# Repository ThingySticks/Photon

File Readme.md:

Photon Prototyping PCB.
=======================

Prototype board for Particle Photon.

See individual versions for PCB specifics.

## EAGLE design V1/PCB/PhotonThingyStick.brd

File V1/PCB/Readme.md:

Photon Prototyping PCB.
=======================

Prototype board for Particle Photon.

Features:
---------

* USB power in via A Connector on left edge or B Connector on Photon. (Do not connect both at once).
* Pull-up or down 1206 pads on A0-A7. Suitable for 1206 or 0805 components.
* LED/Resistor/Capacitor 1206 pads Right edge along with 10 x 2 header for off board connection (8 pins to 1206's + 2v2 & GND).
* 4 1206 pads top/bottom by end of Photon connected to pins to the right of the pad. Ideal of Capacitors, Resistor or LED.
* 3 Mounting holes to allow board to be mounted in case for final use.
* SOT-23 FET/Transistor under Photon with Gate/Base 1206 guard and pull down resistor options.

Mounting:
---------

Single hole middle PCB (at 14.5, 22)
Double holes end PCB (at 76,4 & 76,40)

Size:
-----
Length: 80mm
Width: 44mm

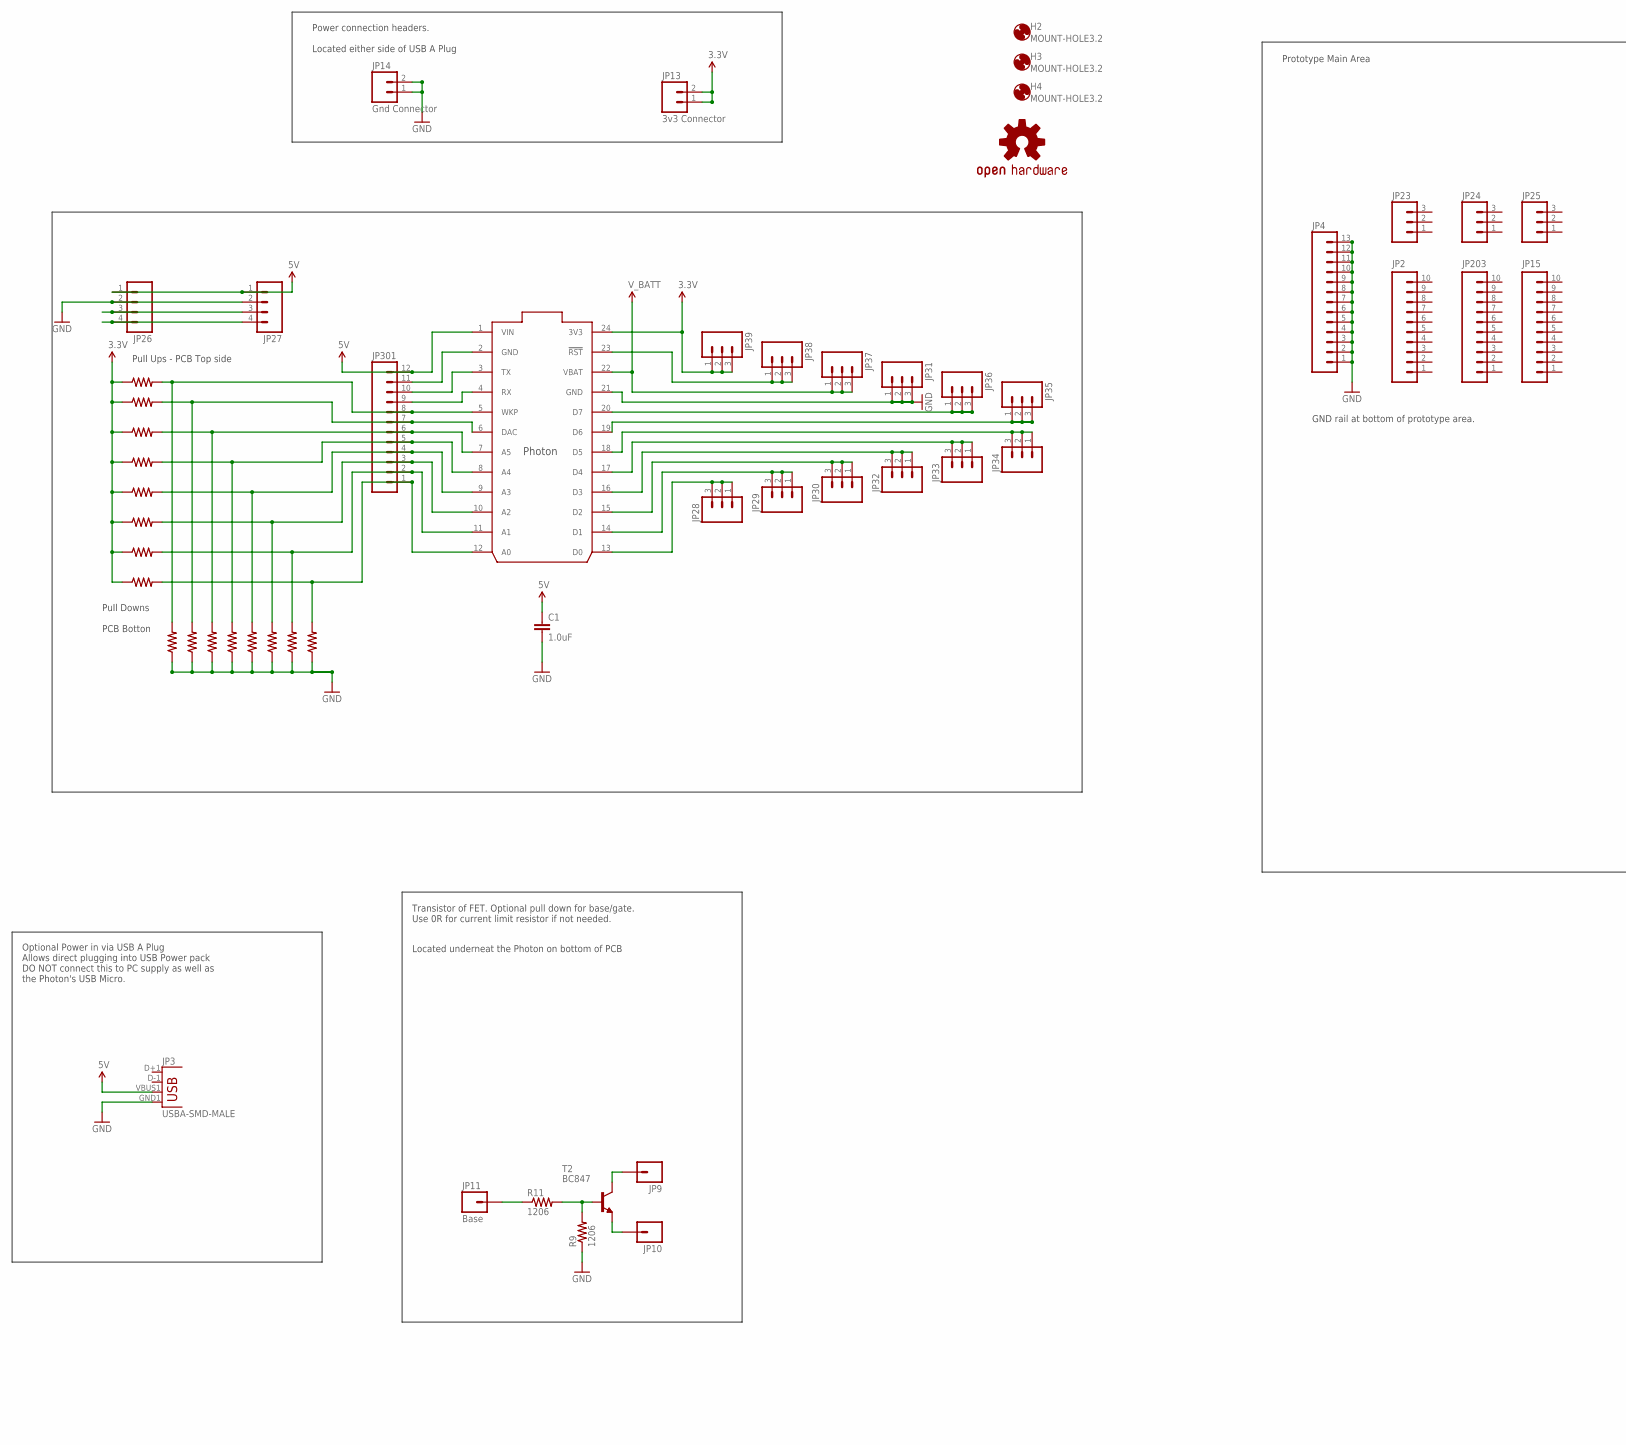
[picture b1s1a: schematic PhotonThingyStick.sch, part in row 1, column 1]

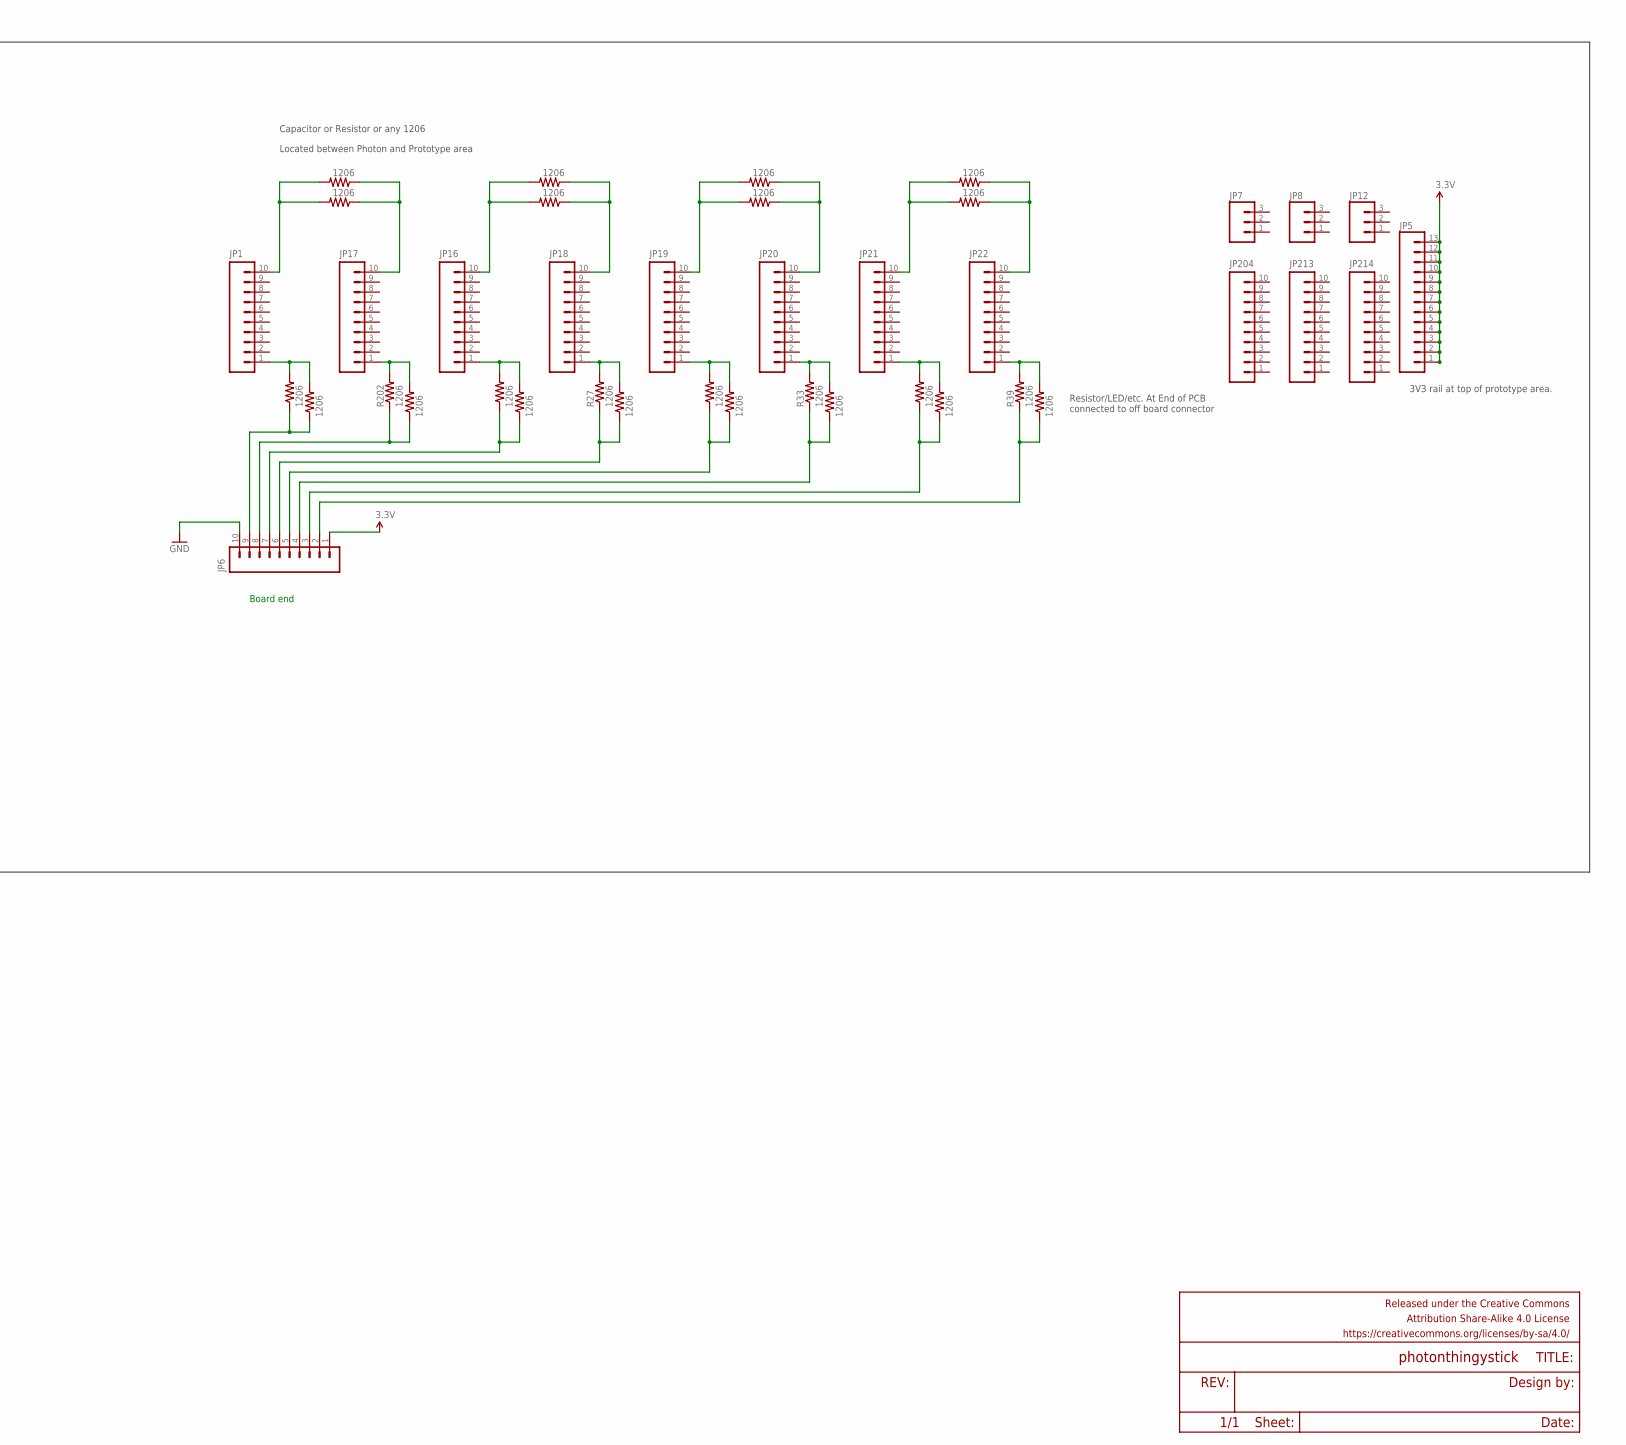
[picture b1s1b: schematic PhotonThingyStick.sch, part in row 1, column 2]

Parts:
C1: 1.0uF; 0805-CAP
FRAME1: FRAME-LEDGER; CREATIVE_COMMONS
H2, H3, H4: MOUNT-HOLE3.2; 3,2
IC1: PHOTON_WITH_HEADERS; PHOTON
JP1, JP2, JP6, JP15, JP16, JP17, JP18, JP19, JP20, JP21, JP22, JP203, JP204, JP213, JP214: M10NO_SILK_PTH_FEMALE; 1X10_NO_SILK
JP3: USBA-SMD-MALE; USB-A-SMT-MALE
JP4, JP5: M13; 1X13
JP7, JP8, JP12, JP23, JP24, JP25: M031X03_NO_SILK; 1X03_NO_SILK
JP9, JP10: M01PTH; 1X01
JP11: Base; 1X01
JP13: 3v3 Connector; 1X02
JP14: Gnd Connector; 1X02
JP26, JP27: M041X04_NO_SILK; 1X04_NO_SILK
JP28, JP29, JP30, JP31, JP32, JP33, JP34, JP35, JP36, JP37, JP38, JP39: M03PTH; 1X03
JP301: M12PTH; 1X12
LOGO1: OSHW-LOGOM; OSHW-LOGO-M
R1, R2, R3, R4, R5, R6, R7, R8, R9, R10, R11, R12, R13, R14, R19, R20, R21, R22, R23, R24, R25, R26, R27, R28, R29, R30, R31, R32, R33, R34, R35, R36, R37, R38, R39, R40, R41, R42, R43, R44, R201, R202: 1206
T2: BC847; SOT23

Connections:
3.3V: IC1.24 (3V3), JP5.1, JP5.2, JP5.3, JP5.4, JP5.5, JP5.6, JP5.7, JP5.8, JP5.9, JP5.10, JP5.11, JP5.12, JP5.13, JP6.1, JP13.1, JP13.2, JP39.1, JP39.2, JP39.3, R1.1, R2.1, R3.1, R4.1, R5.1, R6.1, R7.1, R12.1
5V: C1.1, IC1.1 (VIN), JP3.VBUS1 (VBUS), JP26.1, JP27.1, JP301.12
GND: C1.2, IC1.2 (GND), IC1.21 (GND), JP3.GND1 (GND), JP4.1, JP4.2, JP4.3, JP4.4, JP4.5, JP4.6, JP4.7, JP4.8, JP4.9, JP4.10, JP4.11, JP4.12, JP4.13, JP6.10, JP14.1, JP14.2, JP26.2, JP27.2, JP31.1, JP31.2, JP31.3, JP301.11, R8.1, R9.1, R10.1, R13.1, R14.1, R19.1, R20.1, R21.1, R22.1
unnamed: JP17.1, R26.2, R202.2
unnamed: JP1.1, R23.2, R201.2
unnamed: IC1.5 (WKP), JP301.8, R8.2, R12.2
unnamed: IC1.6 (DAC), JP301.7, R5.2, R10.2
unnamed: IC1.7 (A5), JP301.6, R1.2, R13.2
unnamed: IC1.8 (A4), JP301.5, R2.2, R14.2
unnamed: IC1.9 (A3), JP301.4, R3.2, R19.2
unnamed: IC1.10 (A2), JP301.3, R4.2, R20.2
unnamed: IC1.11 (A1), JP301.2, R6.2, R21.2
unnamed: IC1.12 (A0), JP301.1, R7.2, R22.2
unnamed: JP6.9, R23.1, R201.1
unnamed: IC1.18 (D5), JP34.1, JP34.2, JP34.3
unnamed: IC1.17 (D4), JP33.1, JP33.2, JP33.3
unnamed: IC1.16 (D3), JP32.1, JP32.2, JP32.3
unnamed: IC1.15 (D2), JP30.1, JP30.2, JP30.3
unnamed: IC1.14 (D1), JP29.1, JP29.2, JP29.3
unnamed: IC1.13 (D0), JP28.1, JP28.2, JP28.3
unnamed: JP1.10, R24.2, R25.2
unnamed: IC1.23 (!RST), JP38.1, JP38.2, JP38.3
unnamed: JP17.10, R24.1, R25.1
unnamed: JP6.8, R26.1, R202.1
unnamed: JP18.1, R27.2, R32.2
unnamed: JP16.1, R28.2, R29.2
unnamed: JP6.7, R28.1, R29.1
unnamed: JP16.10, R30.2, R31.2
unnamed: JP18.10, R30.1, R31.1
unnamed: JP6.6, R27.1, R32.1
unnamed: JP20.1, R33.2, R38.2
unnamed: IC1.20 (D7), JP36.1, JP36.2, JP36.3
unnamed: IC1.19 (D6), JP35.1, JP35.2, JP35.3
unnamed: JP19.1, R34.2, R35.2
unnamed: JP6.5, R34.1, R35.1
unnamed: JP19.10, R36.2, R37.2
unnamed: JP20.10, R36.1, R37.1
unnamed: JP6.4, R33.1, R38.1
unnamed: JP22.1, R39.2, R44.2
unnamed: JP11.1, R11.1
unnamed: R9.2, R11.2, T2.1 (B)
unnamed: JP9.1, T2.3 (C)
unnamed: JP10.1, T2.2 (E)
unnamed: JP21.1, R40.2, R41.2
unnamed: JP6.3, R40.1, R41.1
unnamed: JP21.10, R42.2, R43.2
unnamed: JP22.10, R42.1, R43.1
unnamed: JP6.2, R39.1, R44.1
RX: IC1.4 (RX), JP26.4, JP27.4, JP301.9
TX: IC1.3 (TX), JP26.3, JP27.3, JP301.10
V_BATT: IC1.22 (VBAT), JP37.1, JP37.2, JP37.3

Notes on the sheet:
Prototype Main Area
Board end
Pull Ups - PCB Top side
Pull Downs PCB Botton
Capacitor or Resistor or any 1206
Located between Photon and Prototype area
Resistor/LED/etc. At End of PCB connected to off board connector
Transistor of FET. Optional pull down for base/gate. Use 0R for current limit resistor if not needed.
Located underneat the Photon on bottom of PCB
Optional Power in via USB A Plug Allows direct plugging into USB Power pack DO NOT connect this to PC supply as well as the Photon's USB Micro.
Power connection headers. Located either side of USB A Plug
GND rail at bottom of prototype area.
3V3 rail at top of prototype area.

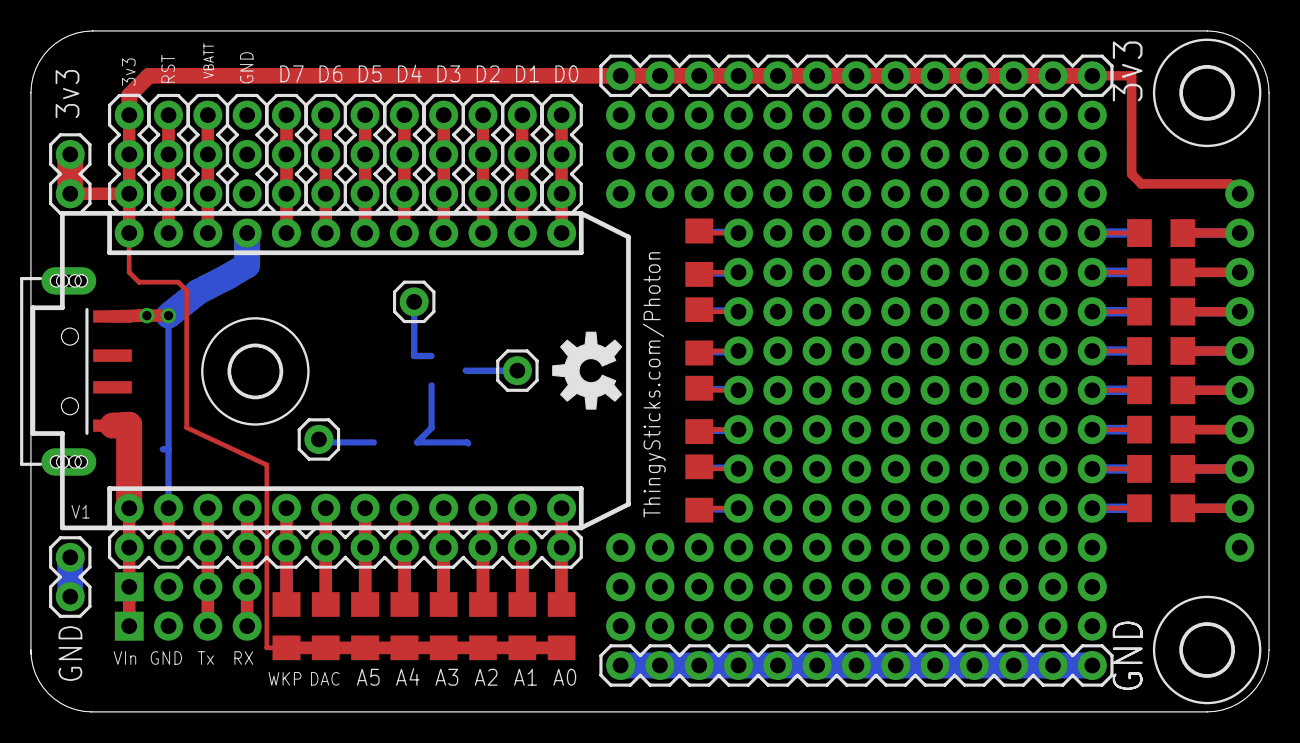
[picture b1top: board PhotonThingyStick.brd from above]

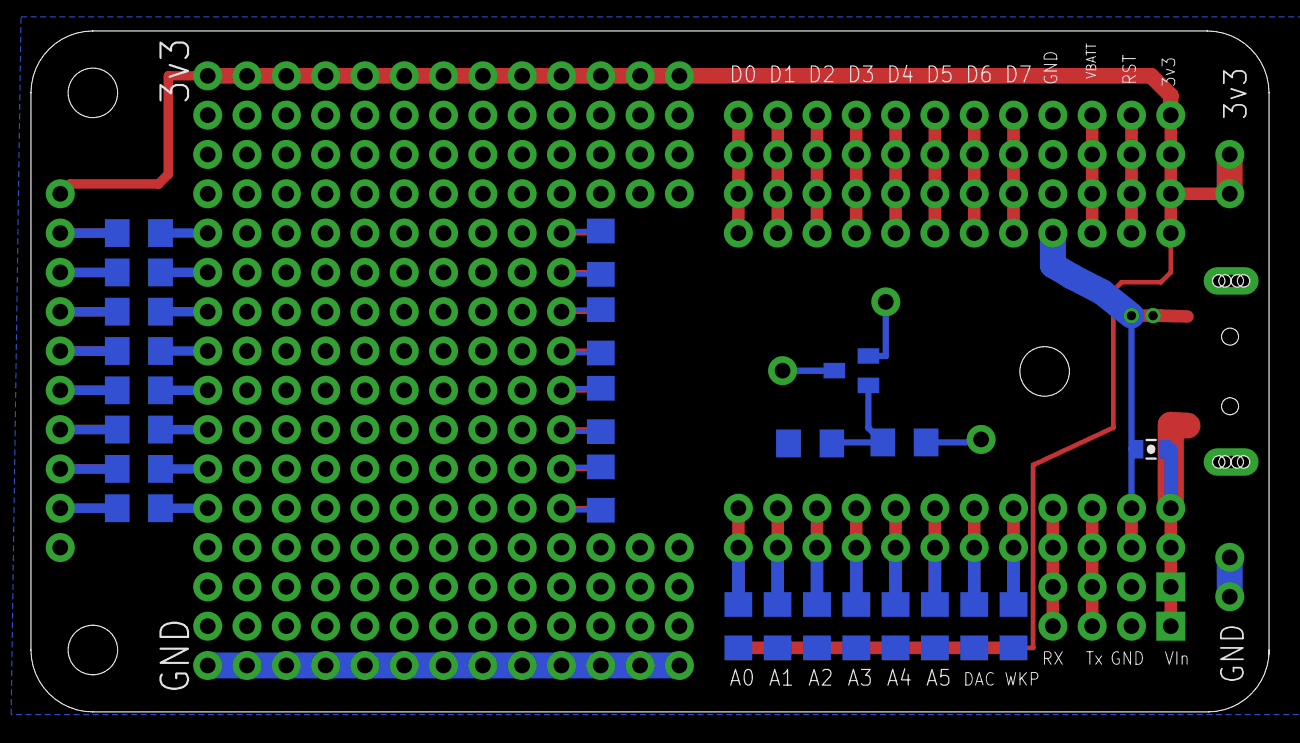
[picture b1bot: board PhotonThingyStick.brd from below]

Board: 2 copper layers, 80.0 x 44.0 mm, 94 parts (24 on the bottom side), 51 nets.

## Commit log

2016-11-18 Moved from Thing On A Stick
    Metricified size and holes.
    Removed 1206 pads on D pins.
    Made end connector 1206's in parralel to save confusion.
    Made end connector single 10 way, 8 data + 3v3 and GND.
    Added OSH Logo.
2016-11-18 Added PDFs and updated hole positions in readme.
2016-11-20 Added DirtyPCB Images.
2016-11-20 Added .gitignore
2017-01-04 Tidied up schematic layout
    Added BOM.
2017-01-04 Fixed json validation issues for BOM.

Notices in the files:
parts and their libraries:
SparkFun-Connectors: Licensing: Creative Commons ShareAlike 4.0 International - https://creativecommons.org/licenses/by-sa/4.0
SparkFun-Aesthetics: Released under the Creative Commons Attribution Share-Alike 4.0 License
SparkFun-Aesthetics: https://creativecommons.org/licenses/by-sa/4.0
